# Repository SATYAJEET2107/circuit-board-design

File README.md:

# circuit-board-design
circuit board design

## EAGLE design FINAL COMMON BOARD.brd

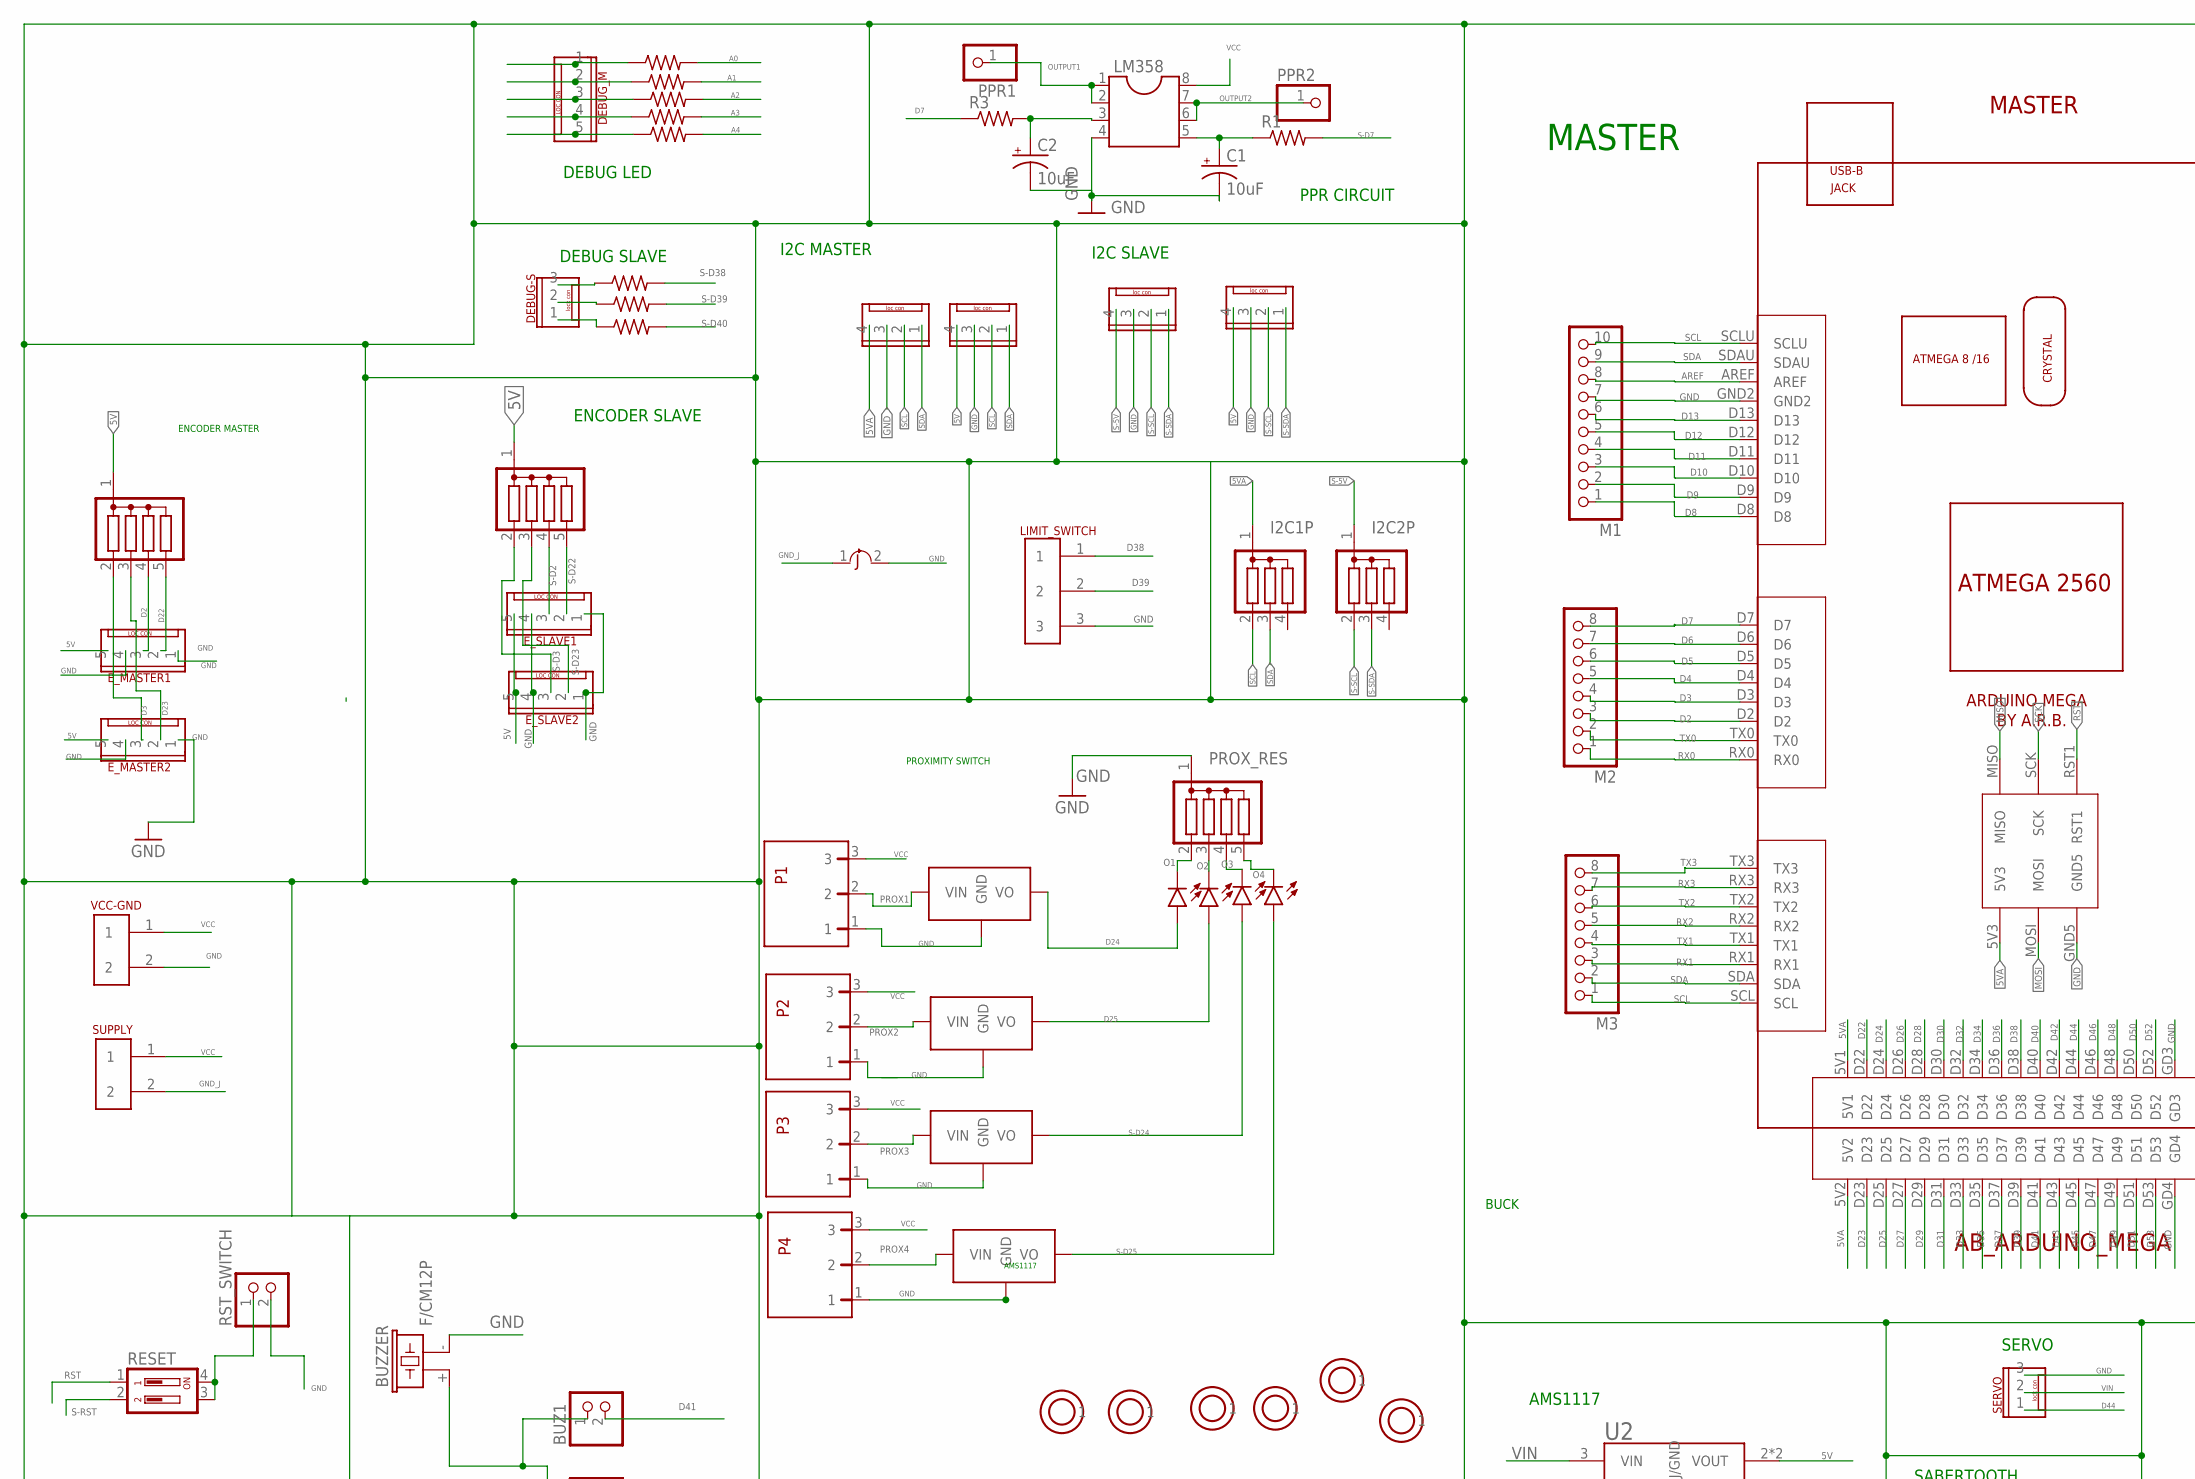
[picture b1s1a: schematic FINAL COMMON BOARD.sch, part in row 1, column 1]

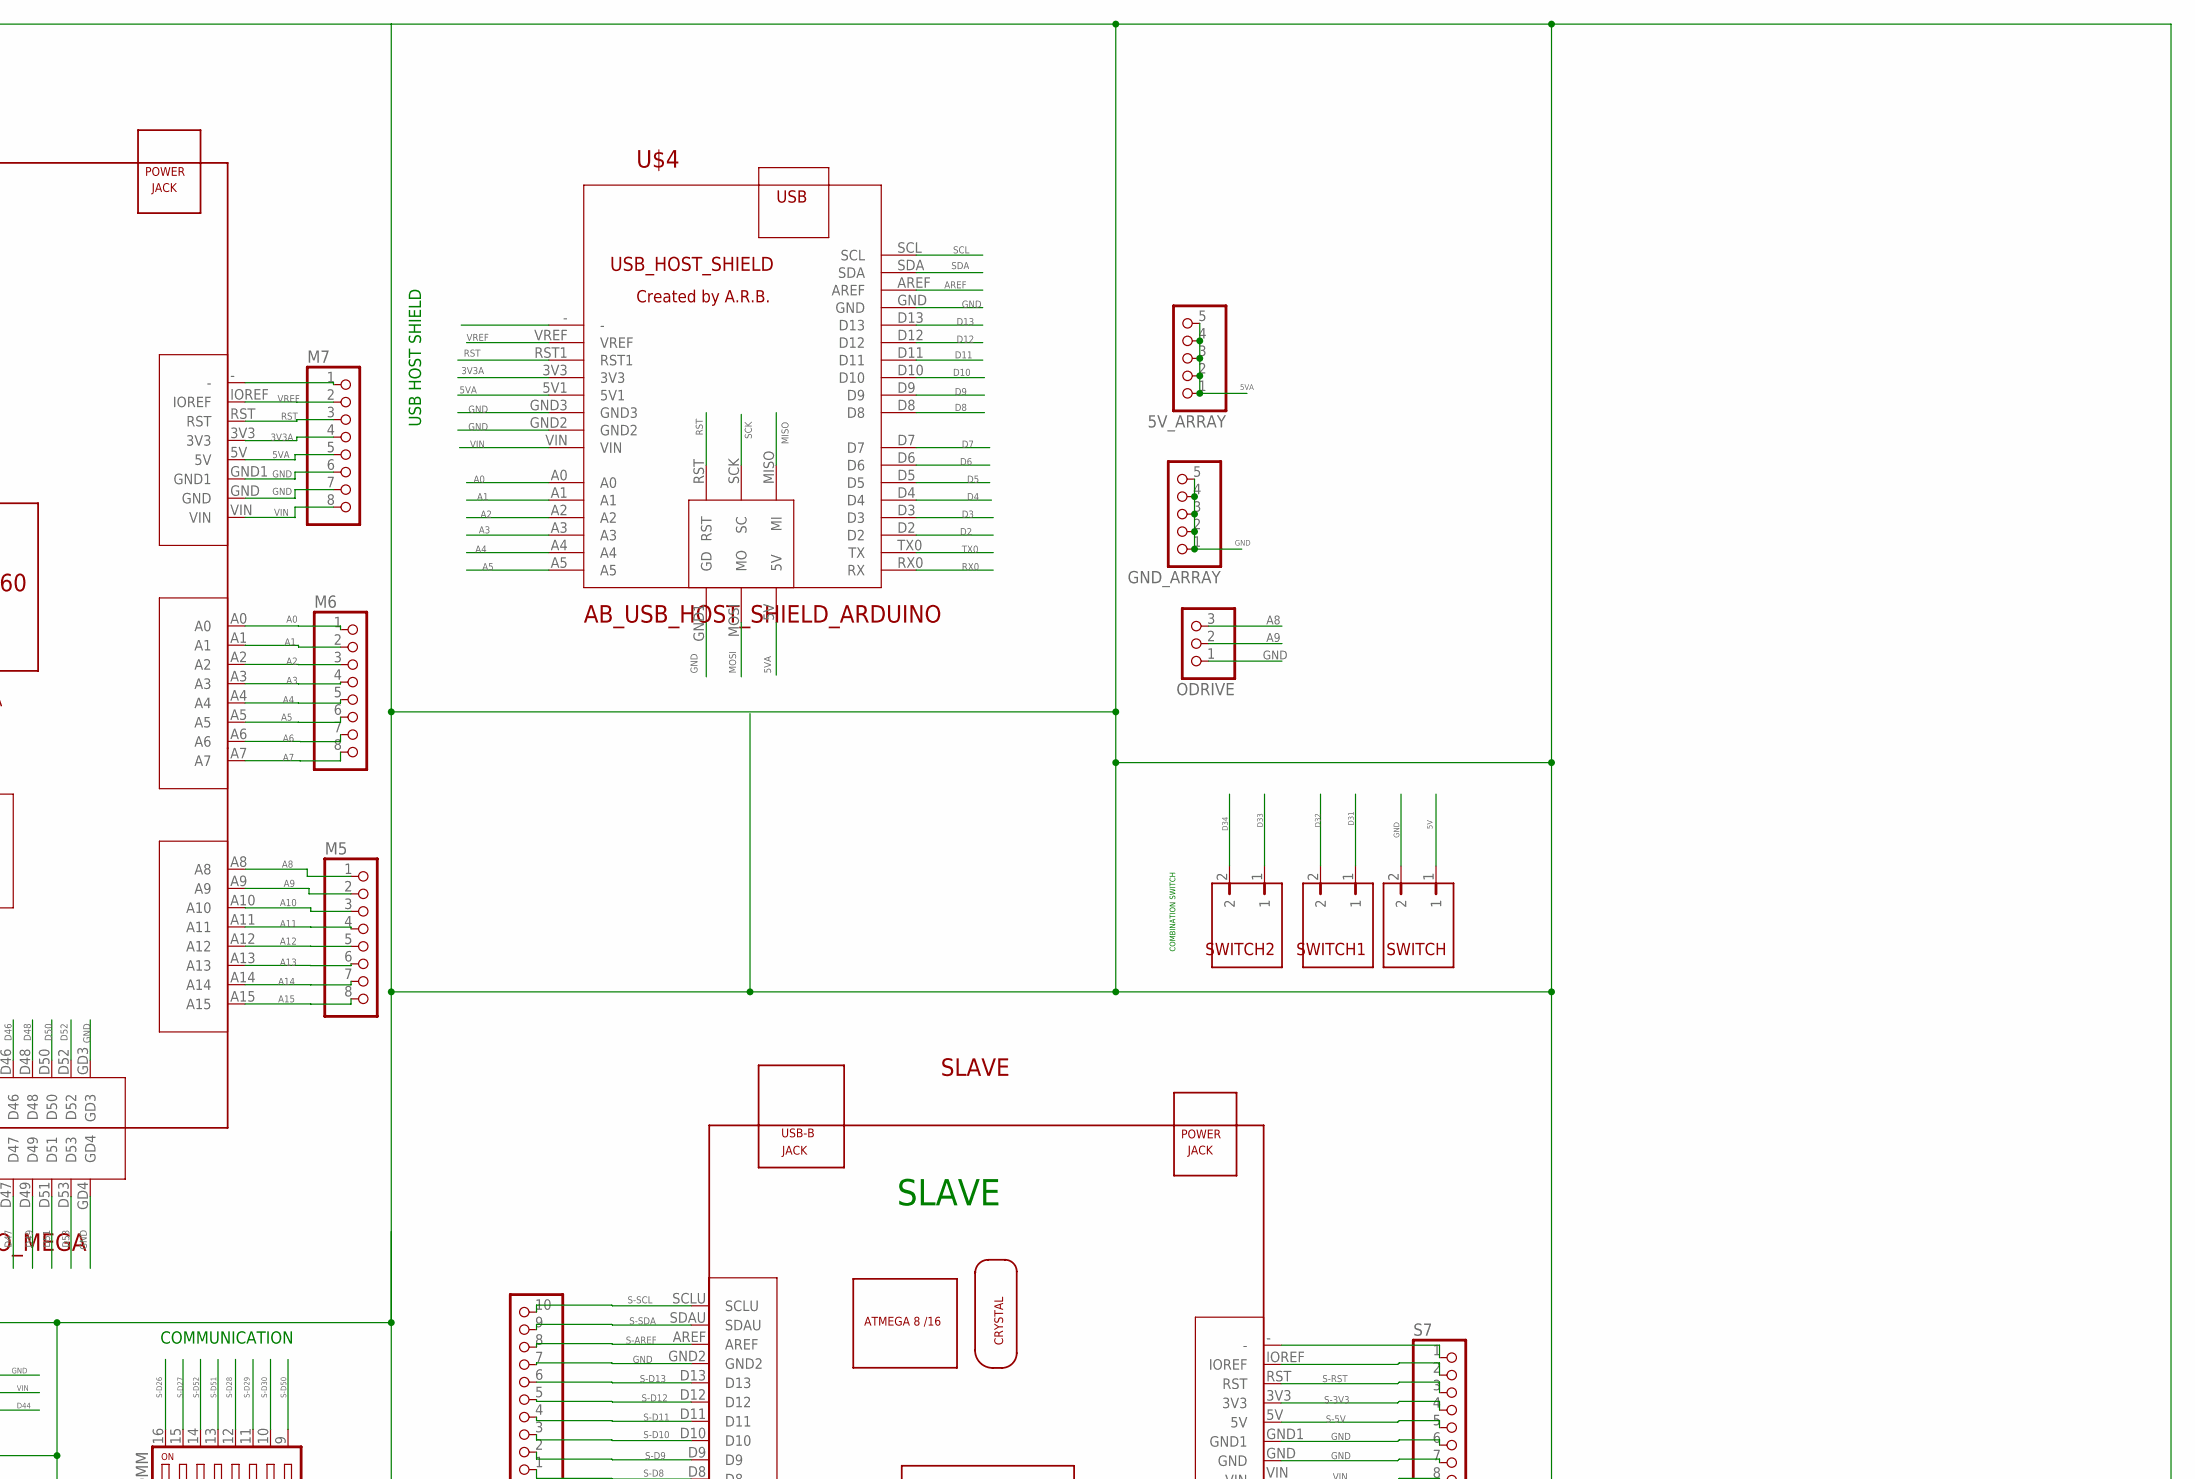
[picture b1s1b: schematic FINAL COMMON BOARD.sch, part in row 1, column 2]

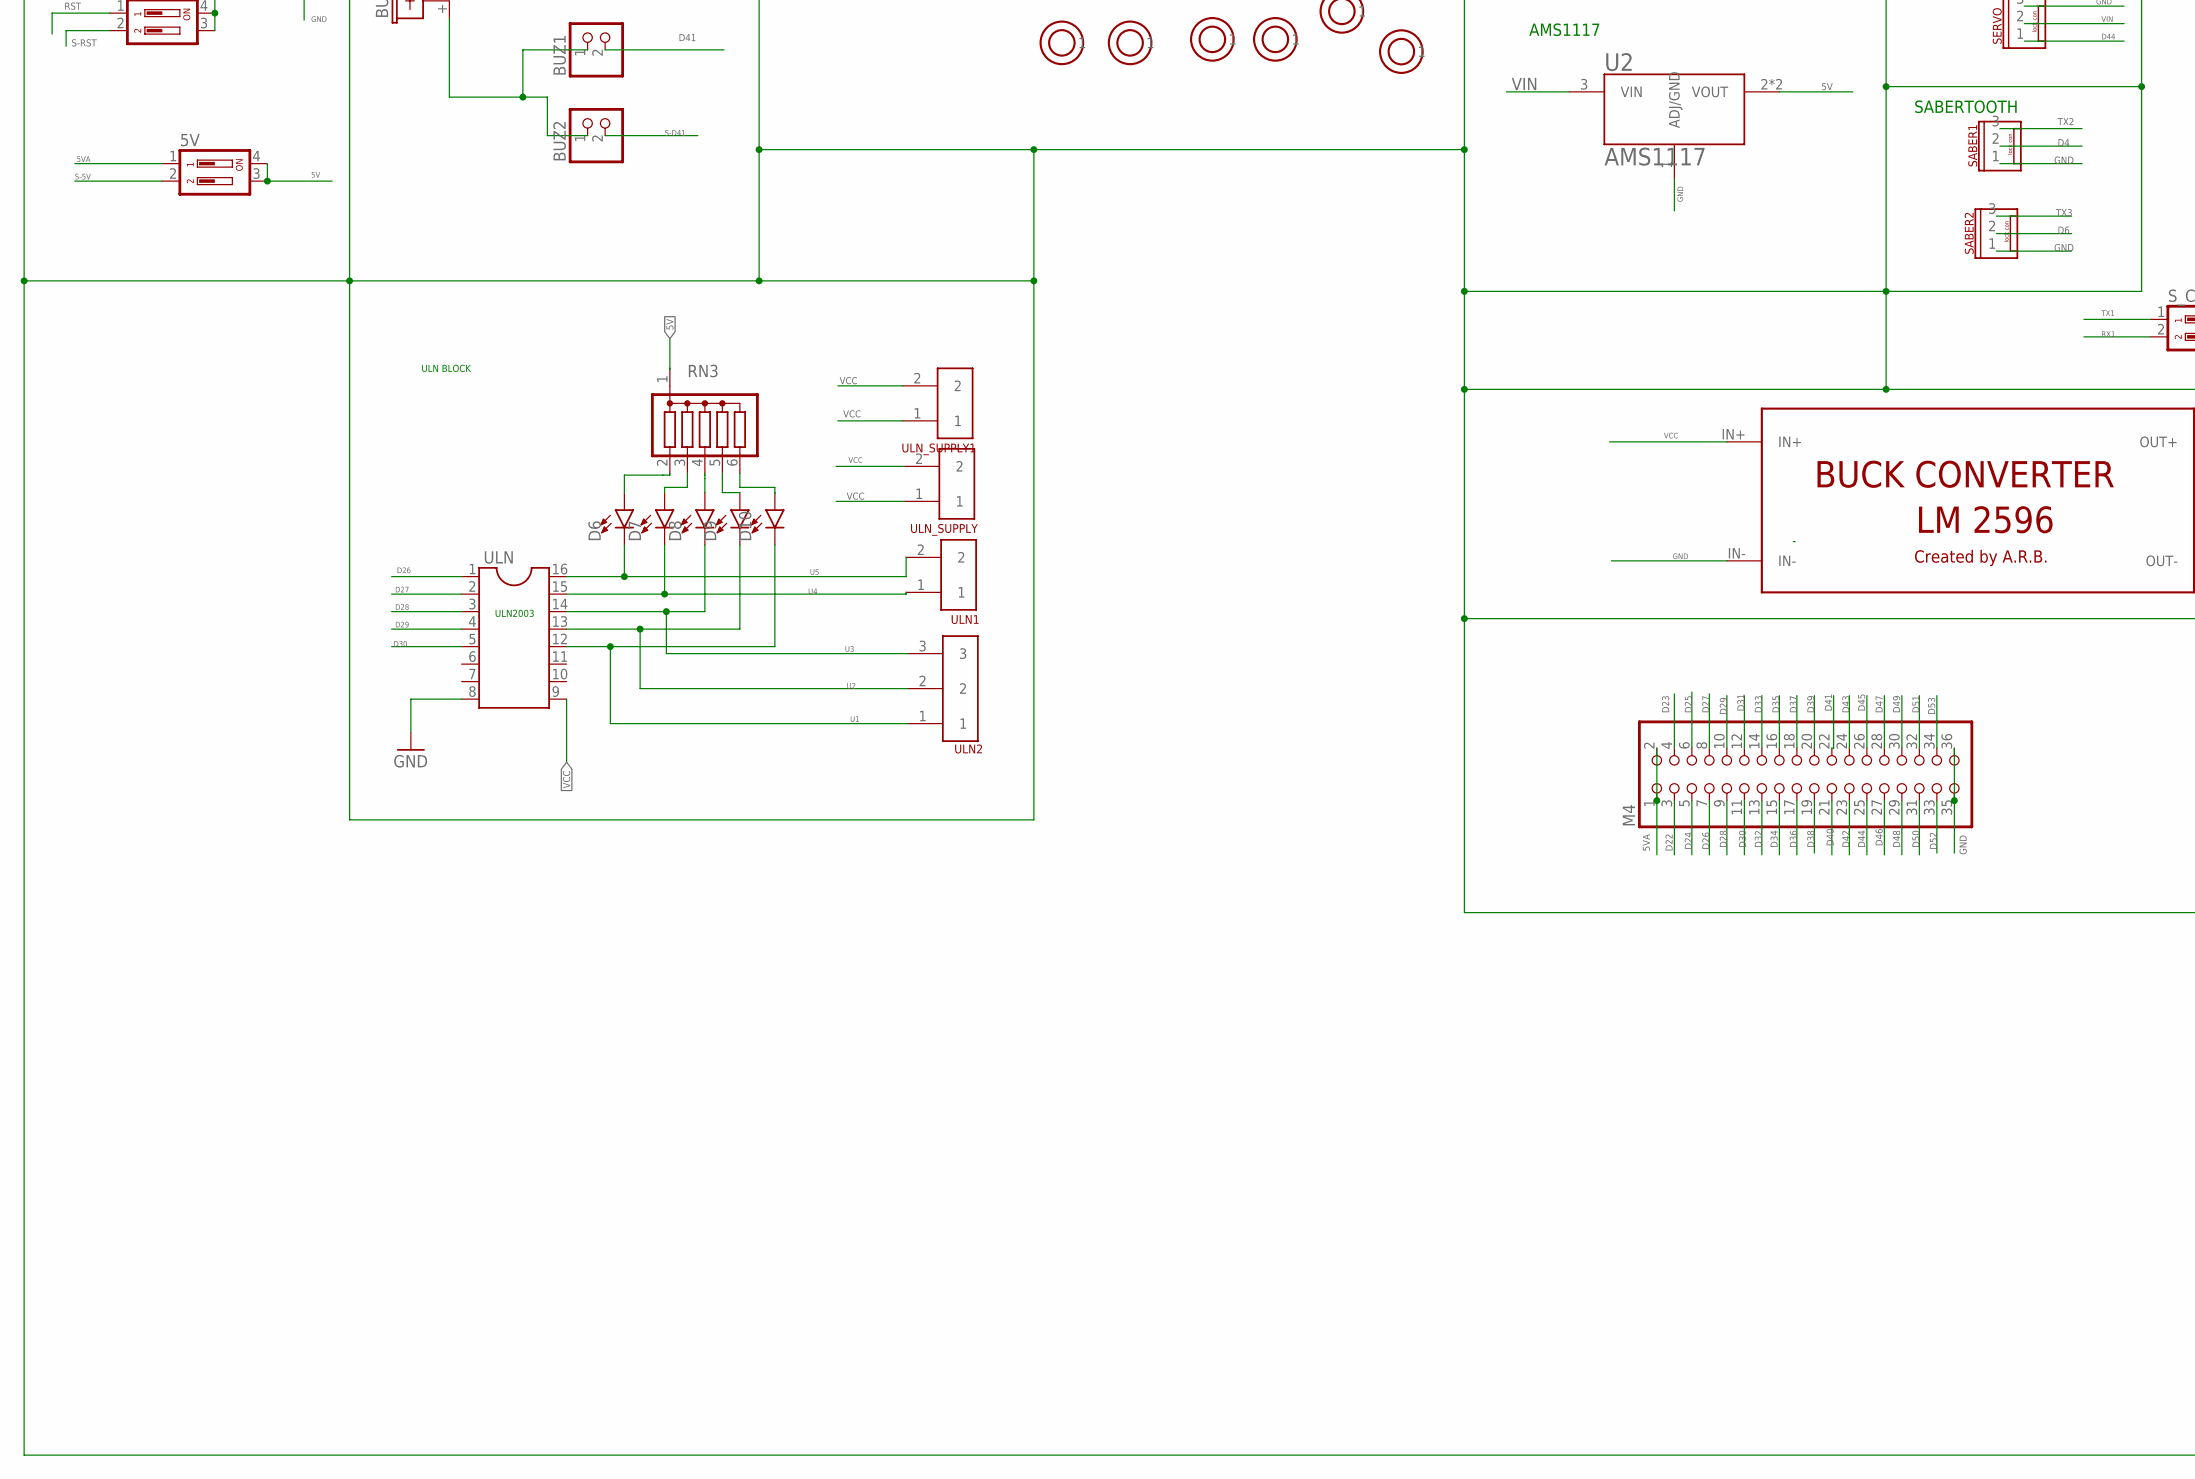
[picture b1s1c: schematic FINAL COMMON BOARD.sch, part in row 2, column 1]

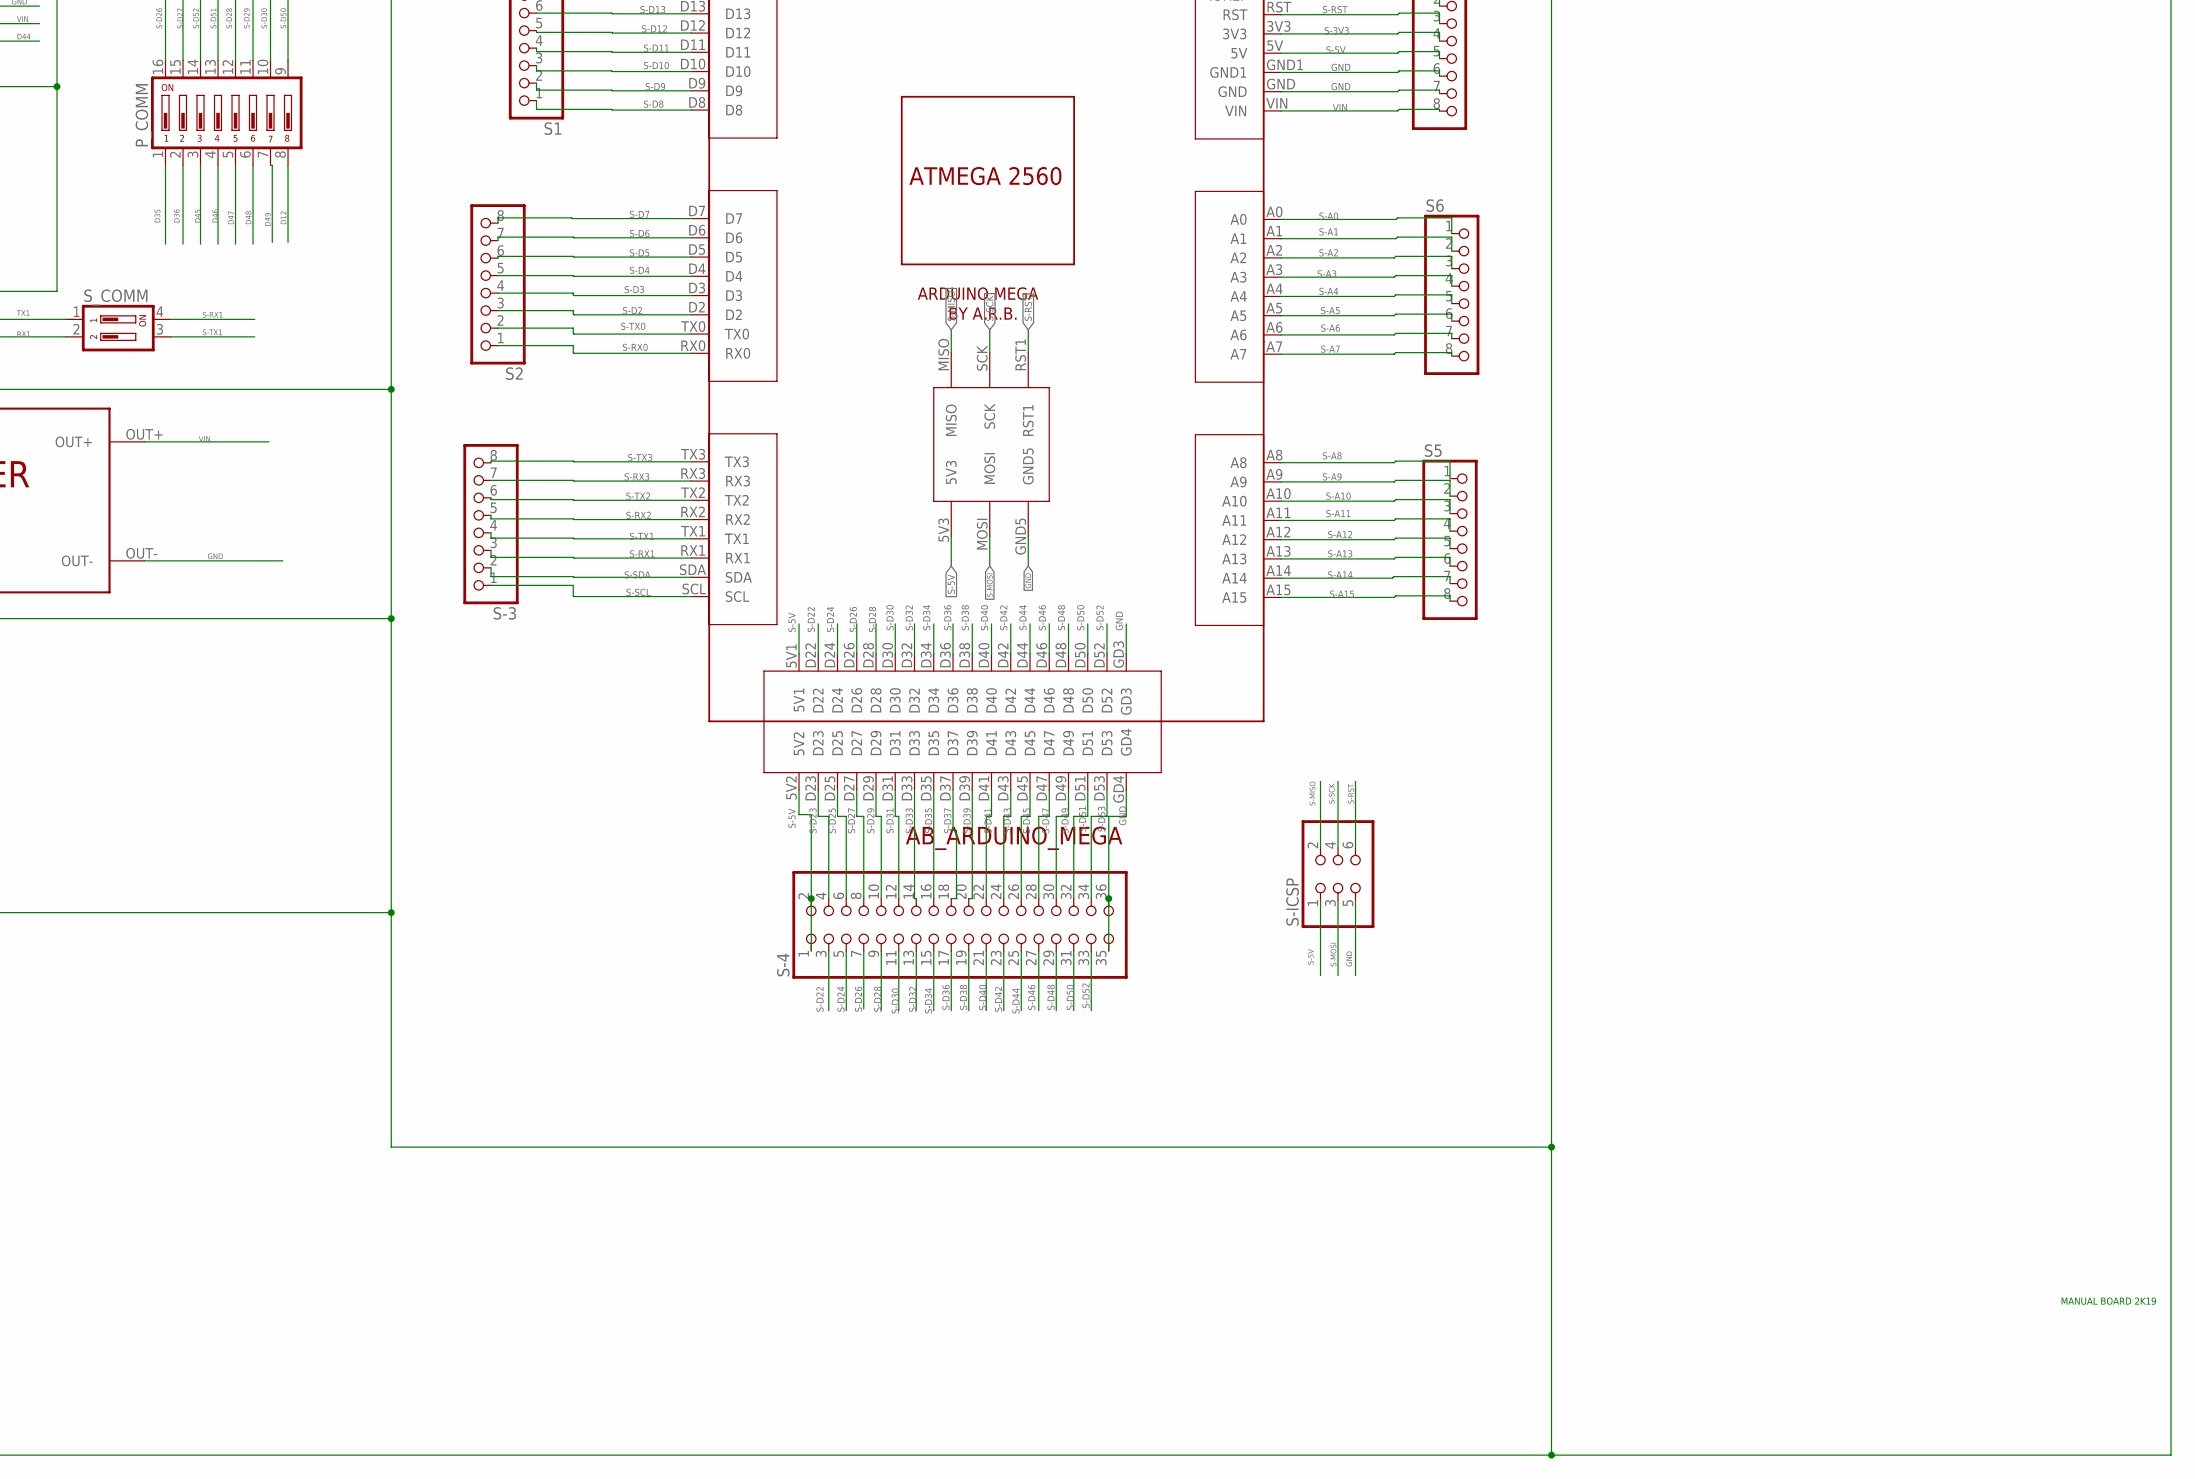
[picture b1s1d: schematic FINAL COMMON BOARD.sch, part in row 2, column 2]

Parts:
5V: DIP02YL
5V_ARRAY: PINHD-1X5; 1X05
BUZ1, BUZ2: PINHD-1X2; 1X02
BUZZER: F/CM12P
C1, C2: 10uF; CPOL-RADIAL-2.5MM-5MM
D1, D2, D3, D6, D7, D8, D9, D10, D14: LED-3MM-NO_SILK; LED_3MM-NS
DEBUG-S: AB_3PIN_LOC_CONNECTOR
DEBUG_M: AB_5PIN_LOC_CONNECTOR
E_MASTER1, E_MASTER2: AB_5PIN_LOC_CONNECTOR
E_SLAVE1, E_SLAVE2: AB_5PIN_LOC_CONNECTOR
GND_ARRAY: PINHD-1X5; 1X05
I2C1P, I2C2P: G03R; SIL4
IMU_BLOCK2, IMU_BLOCK3, IMU_BLOCK4: AB_4PIN_LOC_CONNECTOR
IMU_MASTER: AB_4PIN_LOC_CONNECTOR
LIMIT_SWITCH: AB_SCREW_TER_5MM_3PIN
LM358: DIL8; DIL08
M1: PINHD-1X10; 1X10
M2, M3, M5, M6, M7: PINHD-1X8; 1X08
M4: PINHD-2X18; 2X18
MASTER: AB_ARDUINO_MEGA
ODRIVE: PINHD-1X3; 1X03
P1: P1; AB_RIGHT_TER_BLK_3PIN
P2: P2; AB_RIGHT_TER_BLK_3PIN
P3: P3; AB_RIGHT_TER_BLK_3PIN
P4: P4; AB_RIGHT_TER_BLK_3PIN
PPR1, PPR2: PINHD-1X1; 1X01
PROX_RES: G04R; SIL5
PULL_MASTER: G04R; SIL5
PULL_SLAVE: G04R; SIL5
P_COMM: DIP08YL
R1, R2, R3, R4, R5, R6, R7, R8, R9, R10: R-US_0204/7; 0204/7
RESET: DIP02YL
RN3: G05R; SIL6
RST_SWITCH: PINHD-1X2; 1X02
S1: PINHD-1X10; 1X10
S2, S5, S6, S7: PINHD-1X8; 1X08
S-3: PINHD-1X8; 1X08
S-4: PINHD-2X18; 2X18
S-ICSP: PINHD-2X3; 2X03
SABER1, SABER2: AB_3PIN_LOC_CONNECTOR
SERVO: AB_3PIN_LOC_CONNECTOR
SLAVE: AB_ARDUINO_MEGA
SUPPLY: AB_SCREW_TERMINAL_5MM_2PIN
SWITCH, SWITCH1, SWITCH2: AB_RIGHT_TER_BLK
S_COMM: DIP02YL
U2: AMS1117; SOT229P700X180-4N
U$1, U$2, U$5, U$6, U$7, U$8: PLATED_DRILL_3.5MM
U$3: AB_LM2596_BUCK_CONVERTER
U$4: AB_USB_HOST_SHIELD_ARDUINO
U$23, U$24, U$25, U$26: AB_7805_FLAT
U$35: AB_JUMPER_ONE_WAY
ULN: DIL16
ULN1: AB_SCREW_TERMINAL_5MM_2PIN
ULN2: AB_SCREW_TER_5MM_3PIN
ULN_SUPPLY, ULN_SUPPLY1: AB_SCREW_TERMINAL_5MM_2PIN
VCC-GND: AB_SCREW_TERMINAL_5MM_2PIN

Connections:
3V3A: M7.4, MASTER.3V3, U$4.3V3
5V: 5V.3, 5V.4, E_MASTER1.5, E_MASTER2.5, E_SLAVE1.5, E_SLAVE2.5, IMU_BLOCK2.4, IMU_BLOCK4.4, PULL_MASTER.1, PULL_SLAVE.1, RN3.1, SWITCH.1, U2.2 (VOUT), U2.4 (VOUT)
5VA: 5V.1, 5V_ARRAY.1, 5V_ARRAY.2, 5V_ARRAY.3, 5V_ARRAY.4, 5V_ARRAY.5, I2C1P.1, IMU_MASTER.4, M4.1, M4.2, M7.5, MASTER.5V, MASTER.5V1, MASTER.5V2, MASTER.5V3, U$4.5V, U$4.5V1
A0: M6.1, MASTER.A0, R2.2, U$4.A0
A1: M6.2, MASTER.A1, R4.2, U$4.A1
A2: M6.3, MASTER.A2, R5.2, U$4.A2
A3: M6.4, MASTER.A3, R6.2, U$4.A3
A4: M6.5, MASTER.A4, R7.2, U$4.A4
A5: M6.6, MASTER.A5, U$4.A5
A6: M6.7, MASTER.A6
A7: M6.8, MASTER.A7
A8: M5.1, MASTER.A8, ODRIVE.3
A9: M5.2, MASTER.A9, ODRIVE.2
A10: M5.3, MASTER.A10
A11: M5.4, MASTER.A11
A12: M5.5, MASTER.A12
A13: M5.6, MASTER.A13
A14: M5.7, MASTER.A14
A15: M5.8, MASTER.A15
AREF: M1.8, MASTER.AREF, U$4.AREF
D2: E_MASTER1.3, M2.3, MASTER.D2, PULL_MASTER.4, U$4.D2
D3: E_MASTER2.3, M2.4, MASTER.D3, PULL_MASTER.2, U$4.D3
D4: M2.5, MASTER.D4, SABER1.2, U$4.D4
D5: M2.6, MASTER.D5, U$4.D5
D6: M2.7, MASTER.D6, SABER2.2, U$4.D6
D7: M2.8, MASTER.D7, R3.1, U$4.D7
D8: M1.1, MASTER.D8, U$4.D8
D9: M1.2, MASTER.D9, U$4.D9
D10: M1.3, MASTER.D10, U$4.D10
D11: M1.4, MASTER.D11, U$4.D11
D12: M1.5, MASTER.D12, P_COMM.8, U$4.D12
D13: M1.6, MASTER.D13, U$4.D13
D22: E_MASTER1.2, M4.3, MASTER.D22, PULL_MASTER.5
D23: E_MASTER2.2, M4.4, MASTER.D23, PULL_MASTER.3
D24: D14.A, M4.5, MASTER.D24, U$23.3 (VO)
D25: D1.A, M4.6, MASTER.D25, U$24.3 (VO)
D26: M4.7, MASTER.D26, ULN.1
D27: M4.8, MASTER.D27, ULN.2
D28: M4.9, MASTER.D28, ULN.3
D29: M4.10, MASTER.D29, ULN.4
D30: M4.11, MASTER.D30, ULN.5
D31: M4.12, MASTER.D31, SWITCH1.1
D32: M4.13, MASTER.D32, SWITCH1.2
D33: M4.14, MASTER.D33, SWITCH2.1
D34: M4.15, MASTER.D34, SWITCH2.2
D35: M4.16, MASTER.D35, P_COMM.1
D36: M4.17, MASTER.D36, P_COMM.2
D37: M4.18, MASTER.D37
D38: LIMIT_SWITCH.1, M4.19, MASTER.D38
D39: LIMIT_SWITCH.2, M4.20, MASTER.D39
D40: M4.21, MASTER.D40
D41: BUZ1.2, M4.22, MASTER.D41
D42: M4.23, MASTER.D42
D43: M4.24, MASTER.D43
D44: M4.25, MASTER.D44, SERVO.1
D45: M4.26, MASTER.D45, P_COMM.3
D46: M4.27, MASTER.D46, P_COMM.4
D47: M4.28, MASTER.D47, P_COMM.5
D48: M4.29, MASTER.D48, P_COMM.6
D49: M4.30, MASTER.D49, P_COMM.7
D50: M4.31, MASTER.D50
D51: M4.32, MASTER.D51
D52: M4.33, MASTER.D52
D53: M4.34, MASTER.D53
GND: BUZZER.- (2), C1.2 (-), C2.2 (-), E_MASTER1.1, E_MASTER1.4, E_MASTER2.1, E_MASTER2.4, E_SLAVE1.1, E_SLAVE1.4, E_SLAVE2.1, E_SLAVE2.4, GND_ARRAY.1, GND_ARRAY.2, GND_ARRAY.3, GND_ARRAY.4, GND_ARRAY.5, IMU_BLOCK2.3, IMU_BLOCK3.3, IMU_BLOCK4.3, IMU_MASTER.3, LIMIT_SWITCH.3, LM358.4, M1.7, M4.35, M4.36, M7.6, M7.7, MASTER.GD3, MASTER.GD4, MASTER.GND, MASTER.GND1, MASTER.GND2, MASTER.GND5, ODRIVE.1, P1.1, P2.1, P3.1, P4.1, PROX_RES.1, RST_SWITCH.2, S1.7, S7.6, S7.7, S-4.35, S-4.36, S-ICSP.5, SABER1.1, SABER2.1, SERVO.3, SLAVE.GD3, SLAVE.GD4, SLAVE.GND, SLAVE.GND1, SLAVE.GND2, SLAVE.GND5, SWITCH.2, U2.1 (ADJ/GND), U$3.IN-, U$3.OUT-, U$4.GND, U$4.GND1 (GD), U$4.GND2, U$4.GND3, U$23.2 (GND), U$24.2 (GND), U$25.2 (GND), U$26.2 (GND), U$35.2, ULN.8, VCC-GND.2
GND_J: SUPPLY.2, U$35.1
MISO: MASTER.MISO, U$4.MISO (MI)
MOSI: MASTER.MOSI, U$4.MOSI (MO)
unnamed: C1.1 (+), LM358.5, R1.1
unnamed: M7.1, MASTER.-
unnamed: S7.1, SLAVE.-
unnamed: BUZ1.1, BUZ2.1, BUZZER.+ (1)
unnamed: C2.1 (+), LM358.3, R3.2
unnamed: RESET.3, RESET.4, RST_SWITCH.1
unnamed: DEBUG_M.1, R2.1
unnamed: D6.A, RN3.2
unnamed: D7.A, RN3.3
unnamed: D8.A, RN3.4
unnamed: D9.A, RN3.5
unnamed: D10.A, RN3.6
unnamed: DEBUG_M.2, R4.1
unnamed: DEBUG_M.3, R5.1
unnamed: DEBUG_M.4, R6.1
unnamed: DEBUG_M.5, R7.1
unnamed: DEBUG-S.3, R8.1
unnamed: DEBUG-S.2, R9.1
unnamed: DEBUG-S.1, R10.1
unnamed: S7.2, SLAVE.IOREF
O1: D14.K (C), PROX_RES.2
O2: D1.K (C), PROX_RES.3
O3: D2.K (C), PROX_RES.4
O4: D3.K (C), PROX_RES.5
OUTPUT1: LM358.1, LM358.2, PPR1.1
OUTPUT2: LM358.6, LM358.7, PPR2.1
PROX1: P1.2, U$23.1 (VIN)
PROX2: P2.2, U$24.1 (VIN)
PROX3: P3.2, U$25.1 (VIN)
PROX4: P4.2, U$26.1 (VIN)
RST: M7.3, MASTER.RST, MASTER.RST1, RESET.1, U$4.RST, U$4.RST1
RX0: M2.1, MASTER.RX0, U$4.RX0 (RX)
RX1: M3.3, MASTER.RX1, S_COMM.2
RX2: M3.5, MASTER.RX2
RX3: M3.7, MASTER.RX3
S-3V3: S7.4, SLAVE.3V3
S-5V: 5V.2, I2C2P.1, IMU_BLOCK3.4, S7.5, S-4.1, S-4.2, S-ICSP.1, SLAVE.5V, SLAVE.5V1, SLAVE.5V2, SLAVE.5V3
S-A0: S6.1, SLAVE.A0
S-A1: S6.2, SLAVE.A1
S-A2: S6.3, SLAVE.A2
S-A3: S6.4, SLAVE.A3
S-A4: S6.5, SLAVE.A4
S-A5: S6.6, SLAVE.A5
S-A6: S6.7, SLAVE.A6
S-A7: S6.8, SLAVE.A7
S-A8: S5.1, SLAVE.A8
S-A9: S5.2, SLAVE.A9
S-A10: S5.3, SLAVE.A10
S-A11: S5.4, SLAVE.A11
S-A12: S5.5, SLAVE.A12
S-A13: S5.6, SLAVE.A13
S-A14: S5.7, SLAVE.A14
S-A15: S5.8, SLAVE.A15
S-AREF: S1.8, SLAVE.AREF
S-D2: E_SLAVE1.3, PULL_SLAVE.4, S2.3, SLAVE.D2
S-D3: E_SLAVE2.3, PULL_SLAVE.2, S2.4, SLAVE.D3
S-D4: S2.5, SLAVE.D4
S-D5: S2.6, SLAVE.D5
S-D6: S2.7, SLAVE.D6
S-D7: R1.2, S2.8, SLAVE.D7
S-D8: S1.1, SLAVE.D8
S-D9: S1.2, SLAVE.D9
S-D10: S1.3, SLAVE.D10
S-D11: S1.4, SLAVE.D11
S-D12: S1.5, SLAVE.D12
S-D13: S1.6, SLAVE.D13
S-D22: E_SLAVE1.2, PULL_SLAVE.5, S-4.3, SLAVE.D22
S-D23: E_SLAVE2.2, PULL_SLAVE.3, S-4.4, SLAVE.D23
S-D24: D2.A, S-4.5, SLAVE.D24, U$25.3 (VO)
S-D25: D3.A, S-4.6, SLAVE.D25, U$26.3 (VO)
S-D26: P_COMM.16, S-4.7, SLAVE.D26
S-D27: P_COMM.15, S-4.8, SLAVE.D27
S-D28: P_COMM.12, S-4.9, SLAVE.D28
S-D29: P_COMM.11, S-4.10, SLAVE.D29
S-D30: P_COMM.10, S-4.11, SLAVE.D30
S-D31: S-4.12, SLAVE.D31
S-D32: S-4.13, SLAVE.D32
S-D33: S-4.14, SLAVE.D33
S-D34: S-4.15, SLAVE.D34
S-D35: S-4.16, SLAVE.D35
S-D36: S-4.17, SLAVE.D36
S-D37: S-4.18, SLAVE.D37
S-D38: R8.2, S-4.19, SLAVE.D38
S-D39: R9.2, S-4.20, SLAVE.D39
S-D40: R10.2, S-4.21, SLAVE.D40
S-D41: BUZ2.2, S-4.22, SLAVE.D41
S-D42: S-4.23, SLAVE.D42
S-D43: S-4.24, SLAVE.D43
S-D44: S-4.25, SLAVE.D44
S-D45: S-4.26, SLAVE.D45
S-D46: S-4.27, SLAVE.D46
S-D47: S-4.28, SLAVE.D47
S-D48: S-4.29, SLAVE.D48
S-D49: S-4.30, SLAVE.D49
S-D50: P_COMM.9, S-4.31, SLAVE.D50
S-D51: P_COMM.13, S-4.32, SLAVE.D51
S-D52: P_COMM.14, S-4.33, SLAVE.D52
S-D53: S-4.34, SLAVE.D53
S-MISO: S-ICSP.2, SLAVE.MISO
S-MOSI: S-ICSP.3, SLAVE.MOSI
S-RST: RESET.2, S7.3, S-ICSP.6, SLAVE.RST, SLAVE.RST1
S-RX0: S2.1, SLAVE.RX0
S-RX1: S-3.3, SLAVE.RX1, S_COMM.4
S-RX2: S-3.5, SLAVE.RX2
S-RX3: S-3.7, SLAVE.RX3
S-SCK: S-ICSP.4, SLAVE.SCK
S-SCL: I2C2P.2, IMU_BLOCK3.2, IMU_BLOCK4.2, S1.10, S-3.1, SLAVE.SCL, SLAVE.SCLU
S-SDA: I2C2P.3, IMU_BLOCK3.1, IMU_BLOCK4.1, S1.9, S-3.2, SLAVE.SDA, SLAVE.SDAU
S-TX0: S2.2, SLAVE.TX0
S-TX1: S-3.4, SLAVE.TX1, S_COMM.3
S-TX2: S-3.6, SLAVE.TX2
S-TX3: S-3.8, SLAVE.TX3
SCK: MASTER.SCK, U$4.SCK (SC)
SCL: I2C1P.2, IMU_BLOCK2.2, IMU_MASTER.2, M1.10, M3.1, MASTER.SCL, MASTER.SCLU, U$4.SCL
SDA: I2C1P.3, IMU_BLOCK2.1, IMU_MASTER.1, M1.9, M3.2, MASTER.SDA, MASTER.SDAU, U$4.SDA
TX0: M2.2, MASTER.TX0, U$4.TX0 (TX)
TX1: M3.4, MASTER.TX1, S_COMM.1
TX2: M3.6, MASTER.TX2, SABER1.3
TX3: M3.8, MASTER.TX3, SABER2.3
U1: D10.K (C), ULN.12, ULN2.1
U2: D9.K (C), ULN.13, ULN2.2
U3: D8.K (C), ULN.14, ULN2.3
U4: D7.K (C), ULN.15, ULN1.1
U5: D6.K (C), ULN.16, ULN1.2
VCC: LM358.8, P1.3, P2.3, P3.3, P4.3, SUPPLY.1, U$3.IN+, ULN.9, ULN_SUPPLY.1, ULN_SUPPLY.2, ULN_SUPPLY1.1, ULN_SUPPLY1.2, VCC-GND.1
VIN: M7.8, MASTER.VIN, S7.8, SERVO.2, SLAVE.VIN, U2.3 (VIN), U$3.OUT+, U$4.VIN
VREF: M7.2, MASTER.IOREF, U$4.VREF

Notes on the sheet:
ULN2003
ENCODER MASTER
PROXIMITY SWITCH
ULN BLOCK
USB HOST SHIELD
MANUAL BOARD 2K19
BUCK
ENCODER SLAVE
MASTER
SLAVE
I2C SLAVE
I2C MASTER
PPR CIRCUIT
COMBINATION SWITCH
AMS1117
DEBUG LED
DEBUG SLAVE
SERVO
SABERTOOTH
COMMUNICATION

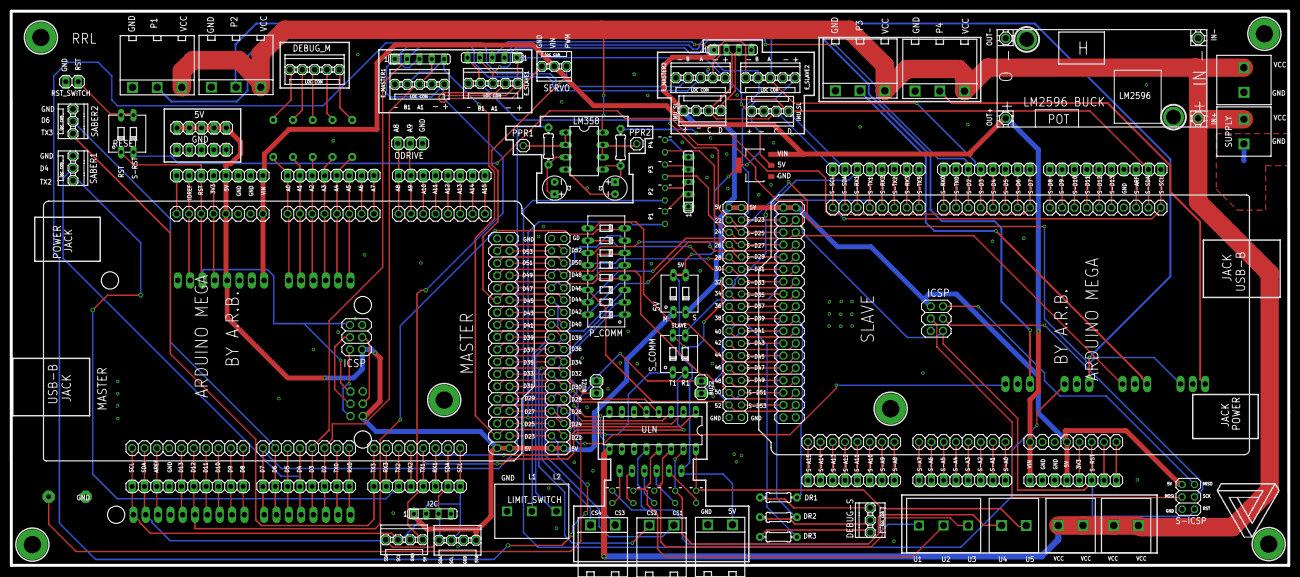
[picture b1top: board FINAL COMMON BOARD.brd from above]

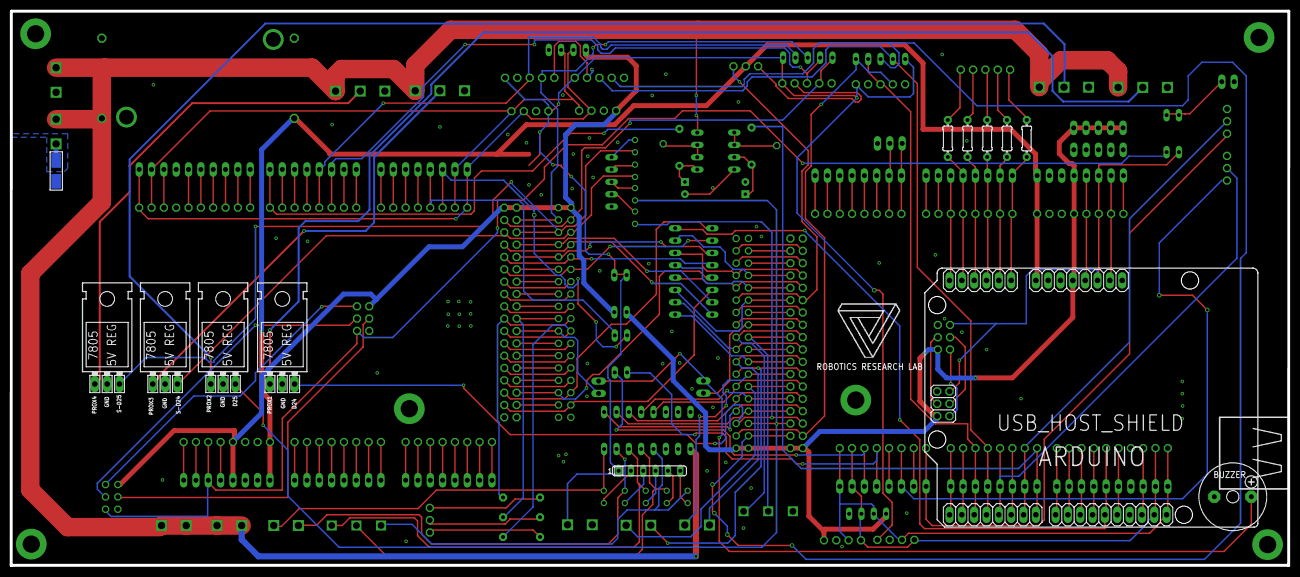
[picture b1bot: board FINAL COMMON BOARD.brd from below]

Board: 2 copper layers, 263.1 x 114.1 mm, 100 parts (13 on the bottom side), 195 nets.

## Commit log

2020-05-12 first project done

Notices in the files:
parts and their libraries:
SparkFun-LED: Licensing: Creative Commons ShareAlike 4.0 International - https://creativecommons.org/licenses/by-sa/4.0
